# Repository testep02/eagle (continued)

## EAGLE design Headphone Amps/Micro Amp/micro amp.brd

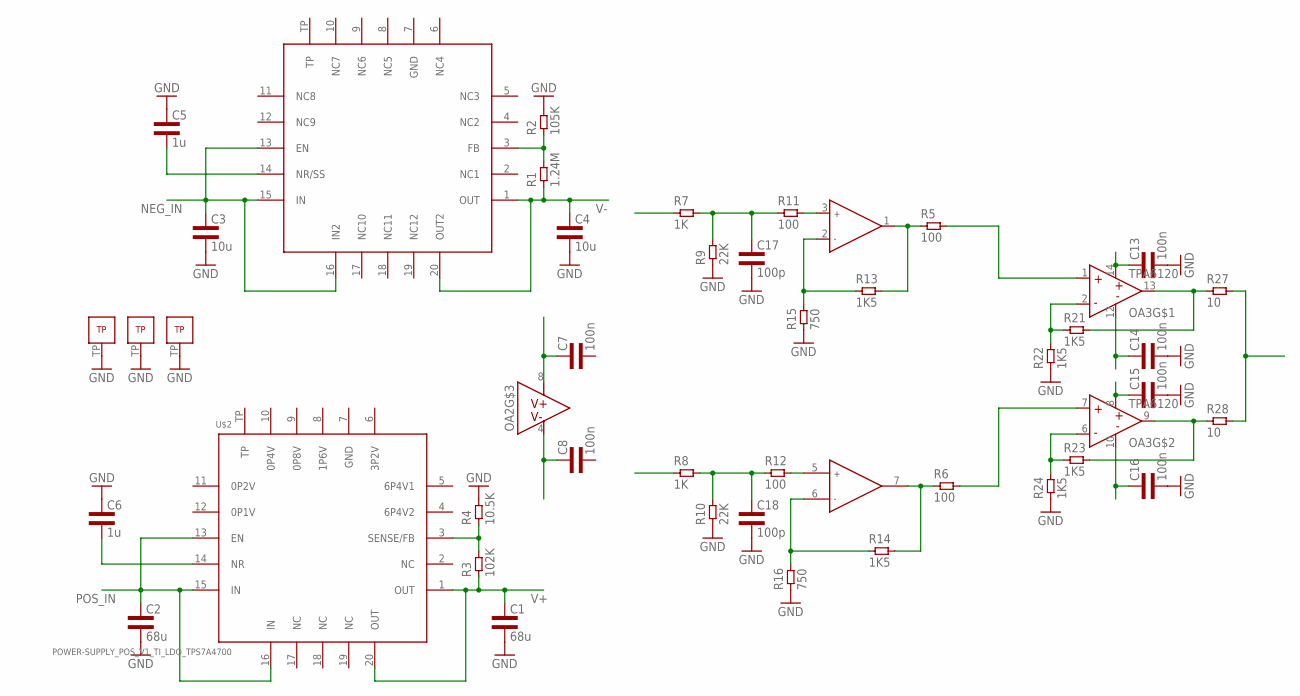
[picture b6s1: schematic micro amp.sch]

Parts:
C1, C2: 68u; 1210L3
C3, C4: 10u; 0805L3
C5, C6: 1u; 0603L3
C7, C8, C13, C14, C15, C16: 100n; 0402L3
C17, C18: 100p; 0402L3
OA1, OA3: TPA6120QFN; S-PVQFN-N14
OA2: OPA1612; S-PWSON-N8
R1: 1.24M; 0402L3
R2: 105K; 0402L3
R3: 102K; 0402L3
R4: 10.5K; 0402L3
R5, R6, R11, R12: 100; 0402L3
R7, R8: 1K; 0402L3
R9, R10: 22K; 0402L3
R13, R14, R21, R22, R23, R24: 1K5; 0402L3
R15, R16: 750; 0402L3
R27, R28: 10; 0805L3
U$1: POWER-SUPPLY_POS_V1_TI_LDO_TPS7A3301RGWT; POWER-SUPPLY_POS_V1_TI_LDO_VQFN-20
U$2: POWER-SUPPLY_POS_V1_TI_LDO_TPS7A4700; POWER-SUPPLY_POS_V1_TI_LDO_VQFN-20

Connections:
GND: C1.P$2 (2), C2.P$2 (2), C3.2, C4.2, C5.P$1 (1), C6.P$1 (1), C13.P$2 (2), C14.P$2 (2), C15.P$2 (2), C16.P$2 (2), C17.P$2 (2), C18.P$2 (2), OA1.TP, OA2.TP, OA3.TP, R2.P$2 (2), R4.P$2 (2), R9.P$1 (1), R10.P$1 (1), R15.P$1 (1), R16.P$1 (1), R22.P$1 (1), R24.P$1 (1)
IN_L: R7.P$1 (1)
IN_R: R8.P$1 (1)
unnamed: R3.P$2 (2), R4.P$1 (1), U$2.3 (SENSE/FB)
unnamed: R1.P$2 (2), R2.P$1 (1), U$1.3 (FB)
unnamed: C5.P$2 (2), U$1.14 (NR/SS)
unnamed: C6.P$2 (2), U$2.14 (NR)
unnamed: OA3.1 (IN+), R5.P$2 (2)
unnamed: OA3.7 (IN+), R6.P$2 (2)
unnamed: OA2.1 (OUTA), R5.P$1 (1), R13.P$2 (2)
unnamed: OA2.7 (OUTB), R6.P$1 (1), R14.P$2 (2)
unnamed: C18.P$1 (1), R8.P$2 (2), R10.P$2 (2), R12.P$1 (1)
unnamed: C17.P$1 (1), R7.P$2 (2), R9.P$2 (2), R11.P$1 (1)
unnamed: OA2.3 (INA+), R11.P$2 (2)
unnamed: OA2.5 (INB+), R12.P$2 (2)
unnamed: OA2.2 (INA-), R13.P$1 (1), R15.P$2 (2)
unnamed: OA2.6 (INB-), R14.P$1 (1), R16.P$2 (2)
unnamed: OA3.13 (OUT), R21.P$2 (2), R27.1
unnamed: OA3.9 (OUT), R23.P$2 (2), R28.1
unnamed: OA3.2 (IN-), R21.P$1 (1), R22.P$2 (2)
unnamed: OA3.6 (IN-), R23.P$1 (1), R24.P$2 (2)
NEG_IN: C3.1, U$1.13 (EN), U$1.15 (IN), U$1.16 (IN2)
OUT_R: R27.2, R28.2
POS_IN: C2.P$1 (1), U$2.13 (EN), U$2.15 (IN), U$2.16 (IN)
V+: C1.P$1 (1), C7.P$1 (1), C13.P$1 (1), C15.P$1 (1), OA2.8 (V+), OA3.8 (V+), OA3.14 (V+), R3.P$1 (1), U$2.1 (OUT), U$2.20 (OUT)
V-: C4.1, C8.P$1 (1), C14.P$1 (1), C16.P$1 (1), OA2.4 (V-), OA3.10 (V-), OA3.12 (V-), R1.P$1 (1), U$1.1 (OUT), U$1.20 (OUT2)

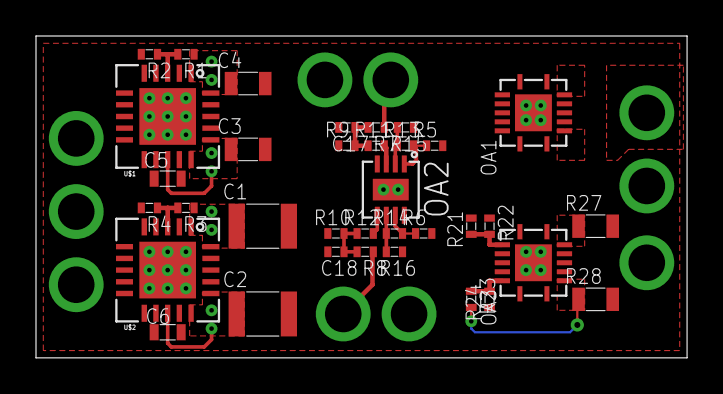
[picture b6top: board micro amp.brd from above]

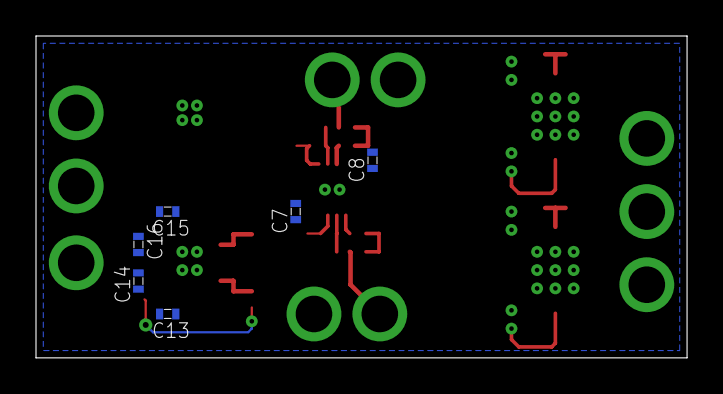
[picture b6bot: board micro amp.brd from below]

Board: 2 copper layers, 36.2 x 17.9 mm, 41 parts (6 on the bottom side), 24 nets.
